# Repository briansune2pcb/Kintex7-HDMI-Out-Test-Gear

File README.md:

# Kintex7-HDMI-Out-Test-Gear

An Test PCB for Kintex 7 FPGA board under Eagle CAD.

An additional KiCAD PCB is also provided.

## T11

```
set_property IOSTANDARD TMDS_33 [get_ports {hdmi_clk[1]}]
set_property IOSTANDARD TMDS_33 [get_ports {hdmi_clk[0]}]
set_property IOSTANDARD TMDS_33 [get_ports {hdmi_d0[1]}]
set_property IOSTANDARD TMDS_33 [get_ports {hdmi_d0[0]}]
set_property IOSTANDARD TMDS_33 [get_ports {hdmi_d1[1]}]
set_property IOSTANDARD TMDS_33 [get_ports {hdmi_d1[0]}]
set_property IOSTANDARD TMDS_33 [get_ports {hdmi_d2[0]}]
set_property IOSTANDARD TMDS_33 [get_ports {hdmi_d2[1]}]

set_property PACKAGE_PIN AG29  [get_ports {hdmi_clk[1]}]
set_property PACKAGE_PIN AC29 [get_ports {hdmi_d0[1]}]
set_property PACKAGE_PIN AB29 [get_ports {hdmi_d1[1]}]
set_property PACKAGE_PIN Y30 [get_ports {hdmi_d2[1]}]
```

## T10

```
set_property IOSTANDARD TMDS_33 [get_ports {hdmi_clk[1]}]
set_property IOSTANDARD TMDS_33 [get_ports {hdmi_clk[0]}]
set_property IOSTANDARD TMDS_33 [get_ports {hdmi_d0[1]}]
set_property IOSTANDARD TMDS_33 [get_ports {hdmi_d0[0]}]
set_property IOSTANDARD TMDS_33 [get_ports {hdmi_d1[1]}]
set_property IOSTANDARD TMDS_33 [get_ports {hdmi_d1[0]}]
set_property IOSTANDARD TMDS_33 [get_ports {hdmi_d2[0]}]
set_property IOSTANDARD TMDS_33 [get_ports {hdmi_d2[1]}]

set_property PACKAGE_PIN F20 [get_ports {hdmi_d0[1]}]
set_property PACKAGE_PIN D17 [get_ports {hdmi_d2[1]}]
set_property PACKAGE_PIN E19 [get_ports {hdmi_d1[1]}]
set_property PACKAGE_PIN C20 [get_ports {hdmi_clk[1]}]
```

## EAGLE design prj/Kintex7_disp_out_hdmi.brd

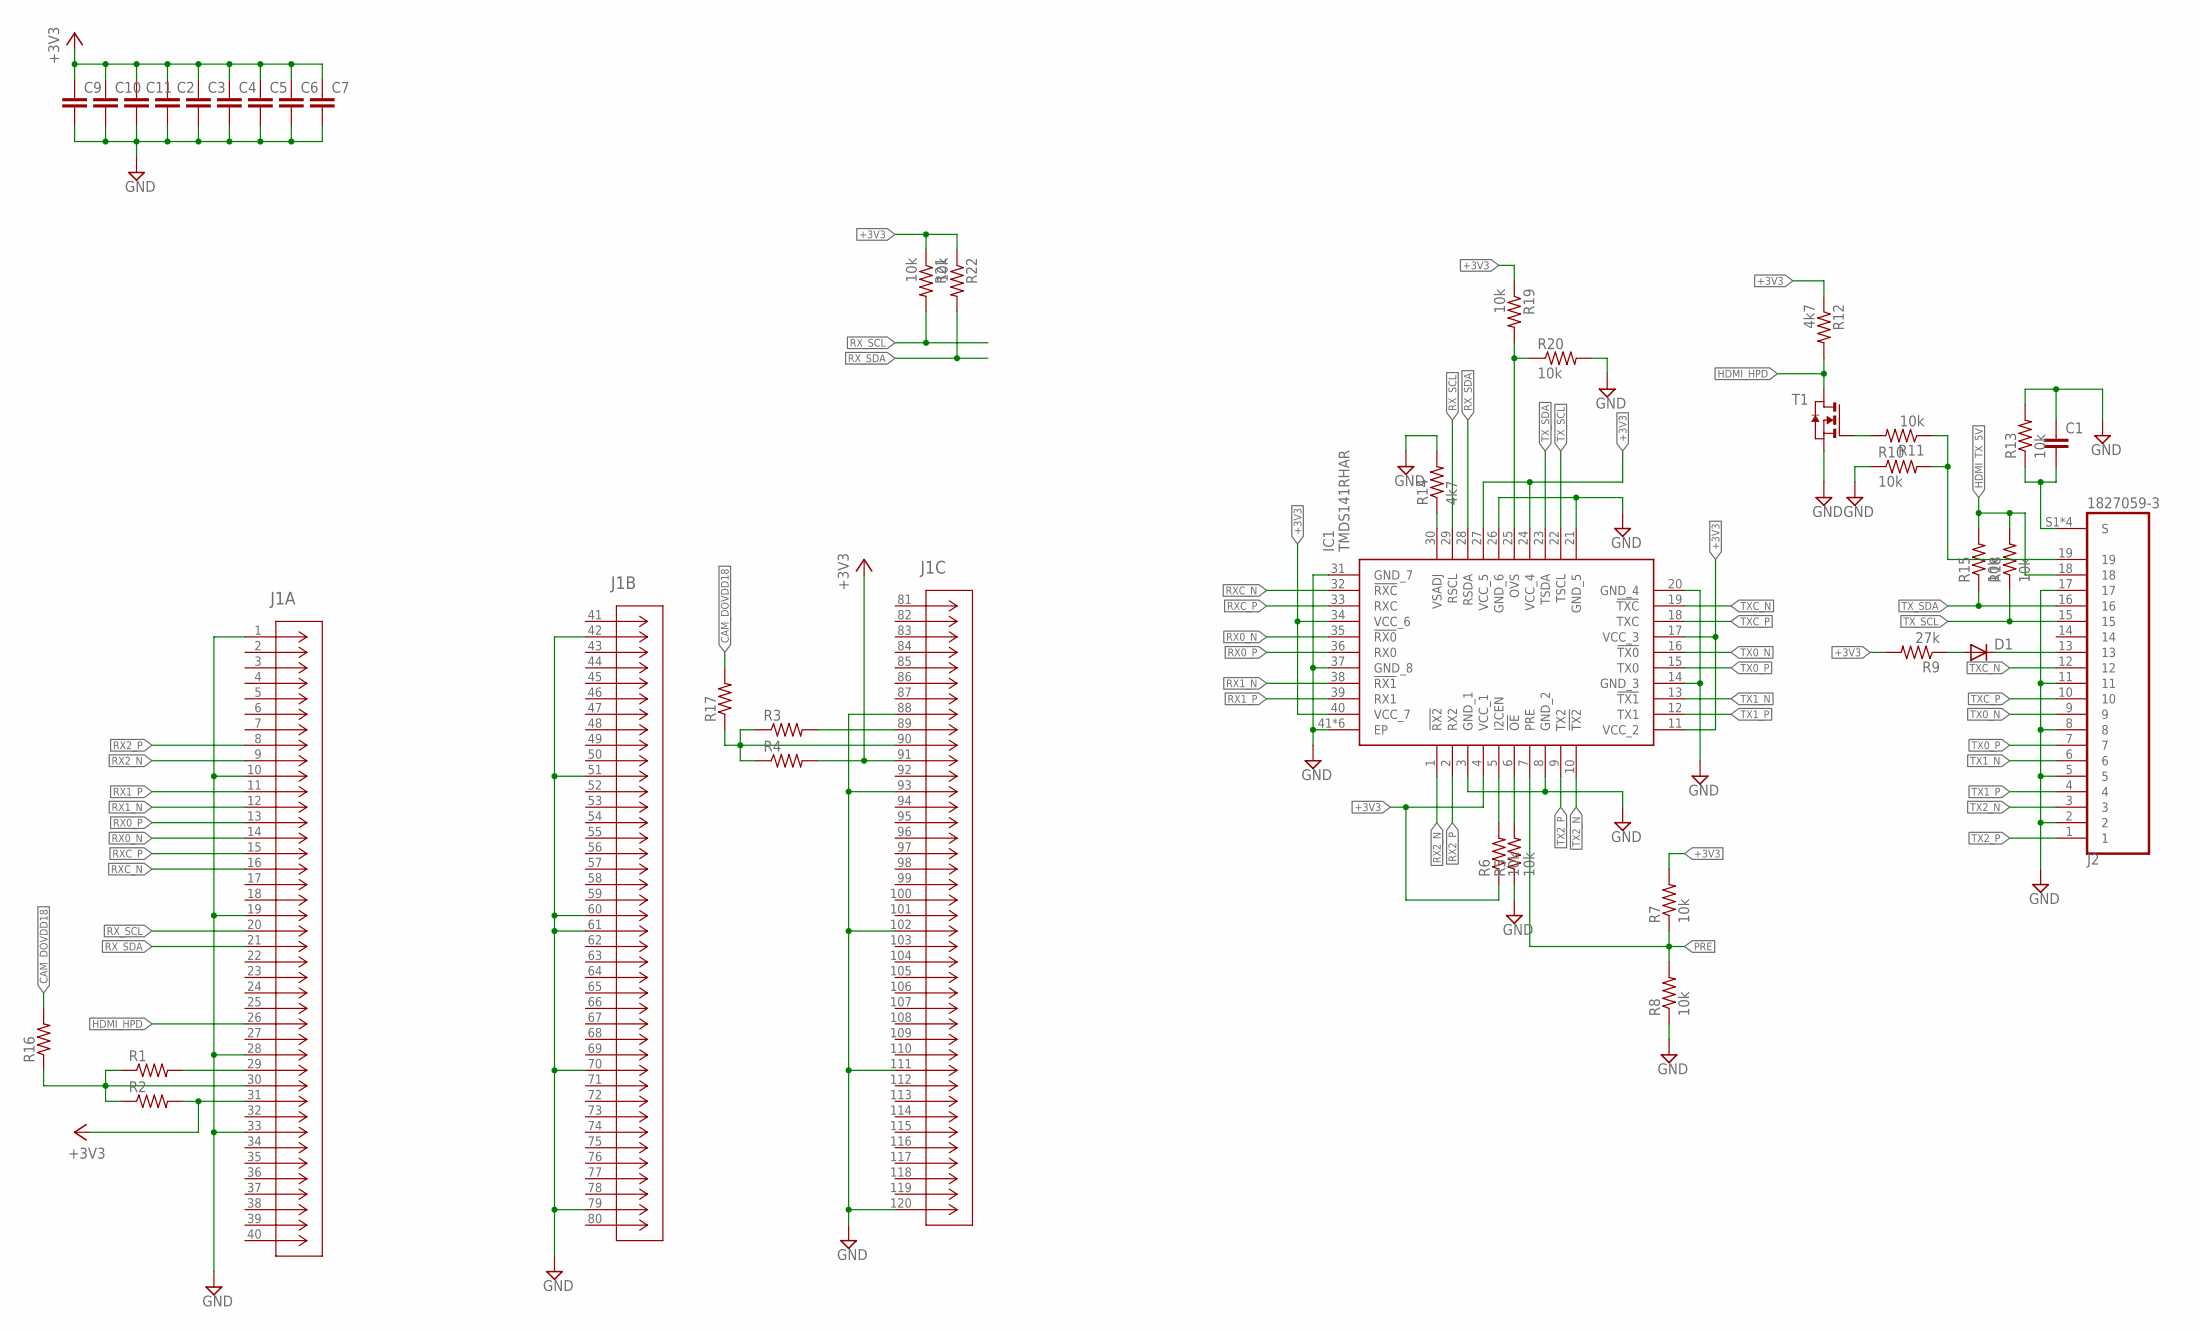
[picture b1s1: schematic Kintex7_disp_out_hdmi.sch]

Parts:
C1, C2, C3, C4, C5, C6, C7, C9, C10, C11: C-EUC0603; C0603
D1: DIODE-MINIMELF; MINIMELF
IC1: TMDS141RHAR; QFN50P600X600X100-41N
J1: 5177985-5; CONN_5177985-5
J2: 1827059-3; TE_1827059-3
R1, R2, R3, R4, R16, R17: R-US_R0805; R0805
R5, R6, R7, R8, R10, R11, R13, R15, R18, R19, R20, R21, R22: 10k; R0805
R9: 27k; R0805
R12, R14: 4k7; R0805
T1: NMOSSOT23; SOT-23

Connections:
+3V3: C2.1, C3.1, C4.1, C5.1, C6.1, C7.1, C9.1, C10.1, C11.1, IC1.4 (VCC_1), IC1.11 (VCC_2), IC1.17 (VCC_3), IC1.24 (VCC_4), IC1.27 (VCC_5), IC1.34 (VCC_6), IC1.40 (VCC_7), J1.31, J1.91, R2.2, R4.2, R6.1, R7.2, R9.2, R12.1, R19.1, R21.1, R22.1
CAM_DOVDD18: R16.2, R17.2
GND: C1.1, C2.2, C3.2, C4.2, C5.2, C6.2, C7.2, C9.2, C10.2, C11.2, IC1.3 (GND_1), IC1.8 (GND_2), IC1.14 (GND_3), IC1.20 (GND_4), IC1.21 (GND_5), IC1.26 (GND_6), IC1.31 (GND_7), IC1.37 (GND_8), IC1.41 (EP), IC1.P$1 (EP), IC1.P$2 (EP), IC1.P$3 (EP), IC1.P$4 (EP), IC1.P$5 (EP), J1.1, J1.10, J1.19, J1.28, J1.33, J1.42, J1.51, J1.60, J1.61, J1.70, J1.79, J1.88, J1.93, J1.102, J1.111, J1.120, J2.2, J2.5, J2.8, J2.11, J2.17, R5.1, R8.1, R10.1, R13.2, R14.2, R20.2, T1.2 (S)
HDMI_HPD: J1.26, R12.2, T1.1 (D)
HDMI_TX_5V: J2.18, R15.2, R18.2
unnamed: D1.A, R9.1
unnamed: J1.90, R3.1, R4.1, R17.1
unnamed: J1.29, R1.2
unnamed: J1.89, R3.2
unnamed: IC1.6 (!OE), R5.2
unnamed: IC1.5 (I2CEN), R6.2
unnamed: D1.C, J2.13
unnamed: J1.30, R1.1, R2.1, R16.1
unnamed: IC1.25 (OVS), R19.2, R20.1
unnamed: R11.2, T1.3 (G)
unnamed: C1.2, J2.S1 (S), J2.S2 (S), J2.S3 (S), J2.S4 (S), R13.1
unnamed: IC1.30 (VSADJ), R14.1
unnamed: J2.19, R10.2, R11.1
PRE: IC1.7 (PRE), R7.1, R8.2
RX0_N: IC1.35 (!RX0), J1.14
RX0_P: IC1.36 (RX0), J1.13
RX1_N: IC1.38 (!RX1), J1.12
RX1_P: IC1.39 (RX1), J1.11
RX2_N: IC1.1 (!RX2), J1.9
RX2_P: IC1.2 (RX2), J1.8
RXC_N: IC1.32 (!RXC), J1.16
RXC_P: IC1.33 (RXC), J1.15
RX_SCL: IC1.29 (RSCL), J1.20, R21.2
RX_SDA: IC1.28 (RSDA), J1.21, R22.2
TX0_N: IC1.16 (!TX0), J2.9
TX0_P: IC1.15 (TX0), J2.7
TX1_N: IC1.13 (!TX1), J2.6
TX1_P: IC1.12 (TX1), J2.4
TX2_N: IC1.10 (!TX2), J2.3
TX2_P: IC1.9 (TX2), J2.1
TXC_N: IC1.19 (!TXC), J2.12
TXC_P: IC1.18 (TXC), J2.10
TX_SCL: IC1.22 (TSCL), J2.15, R18.1
TX_SDA: IC1.23 (TSDA), J2.16, R15.1

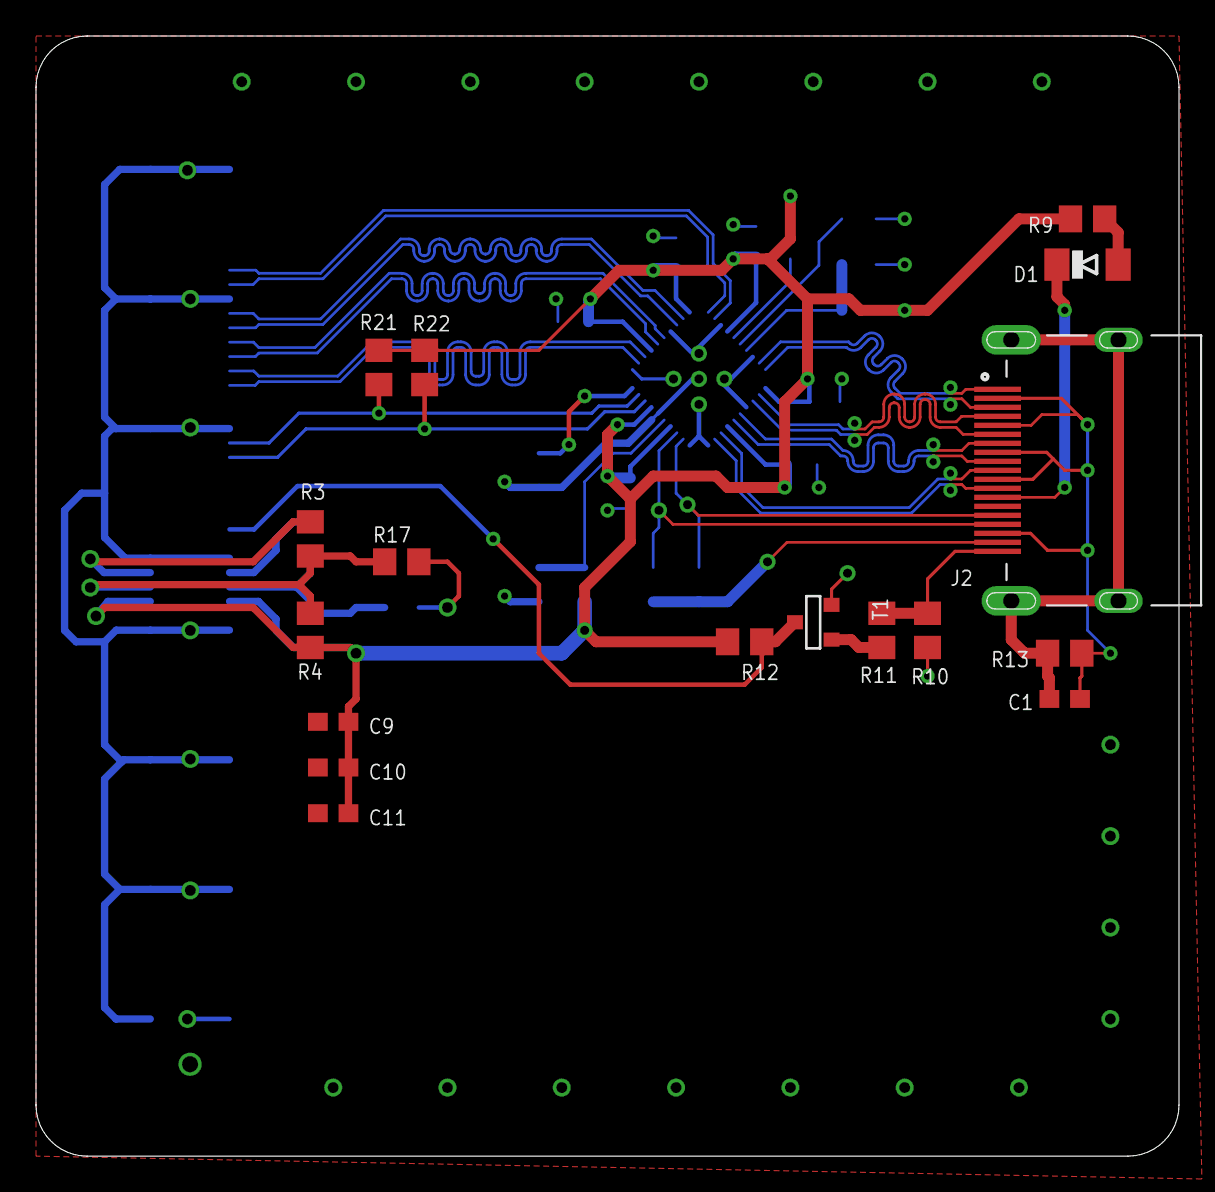
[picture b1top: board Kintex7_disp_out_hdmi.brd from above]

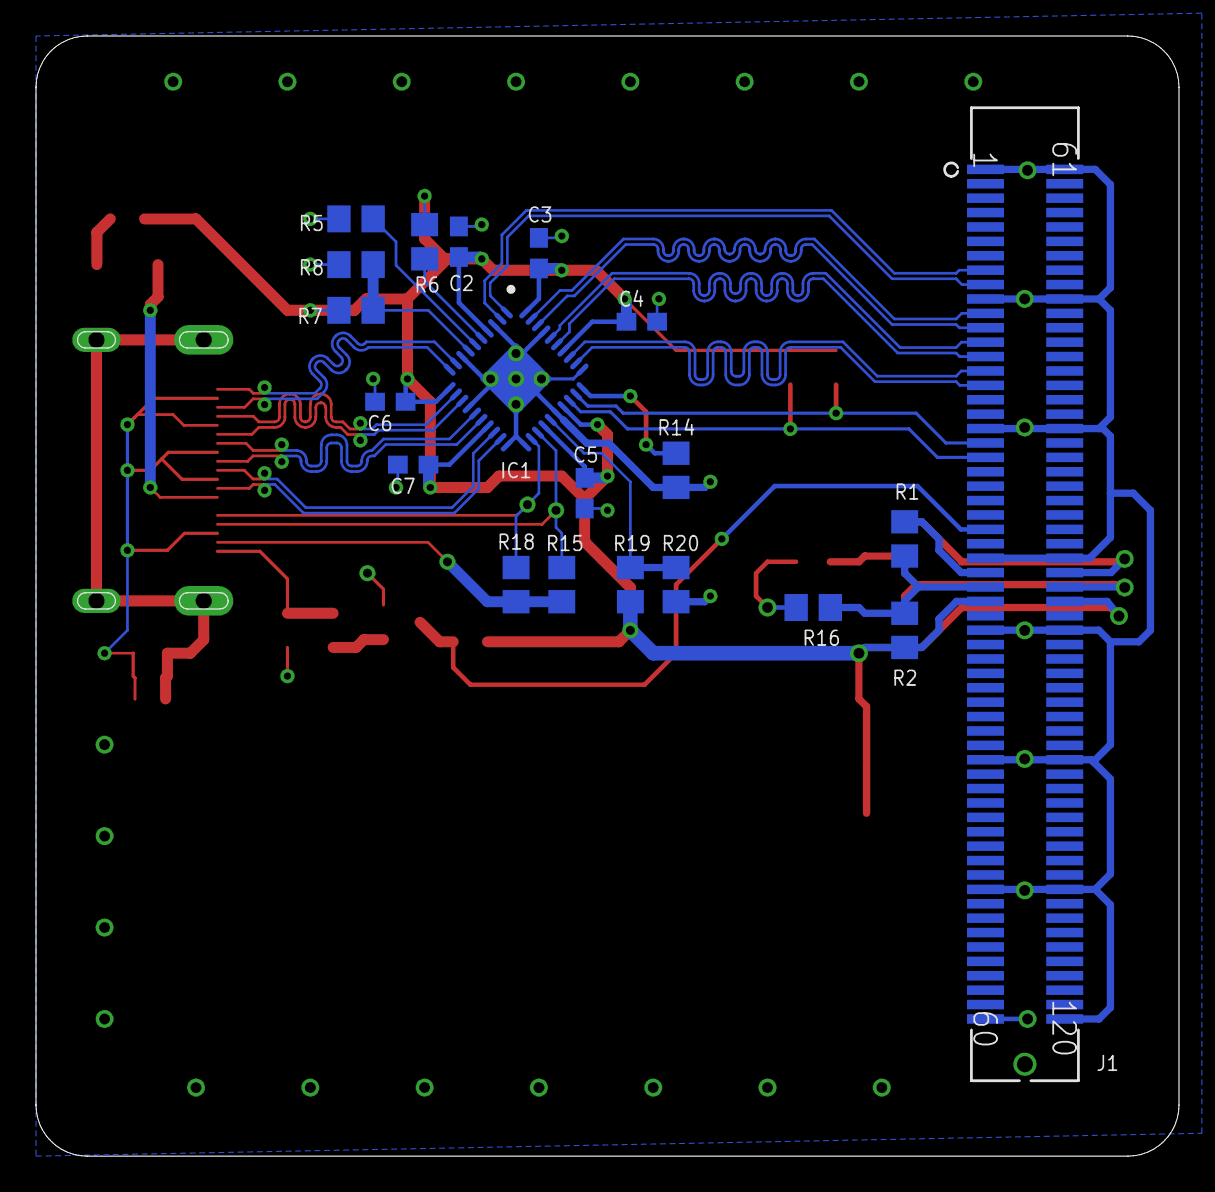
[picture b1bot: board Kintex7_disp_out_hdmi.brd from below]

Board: 2 copper layers, 63.5 x 62.2 mm, 37 parts (20 on the bottom side), 39 nets.
